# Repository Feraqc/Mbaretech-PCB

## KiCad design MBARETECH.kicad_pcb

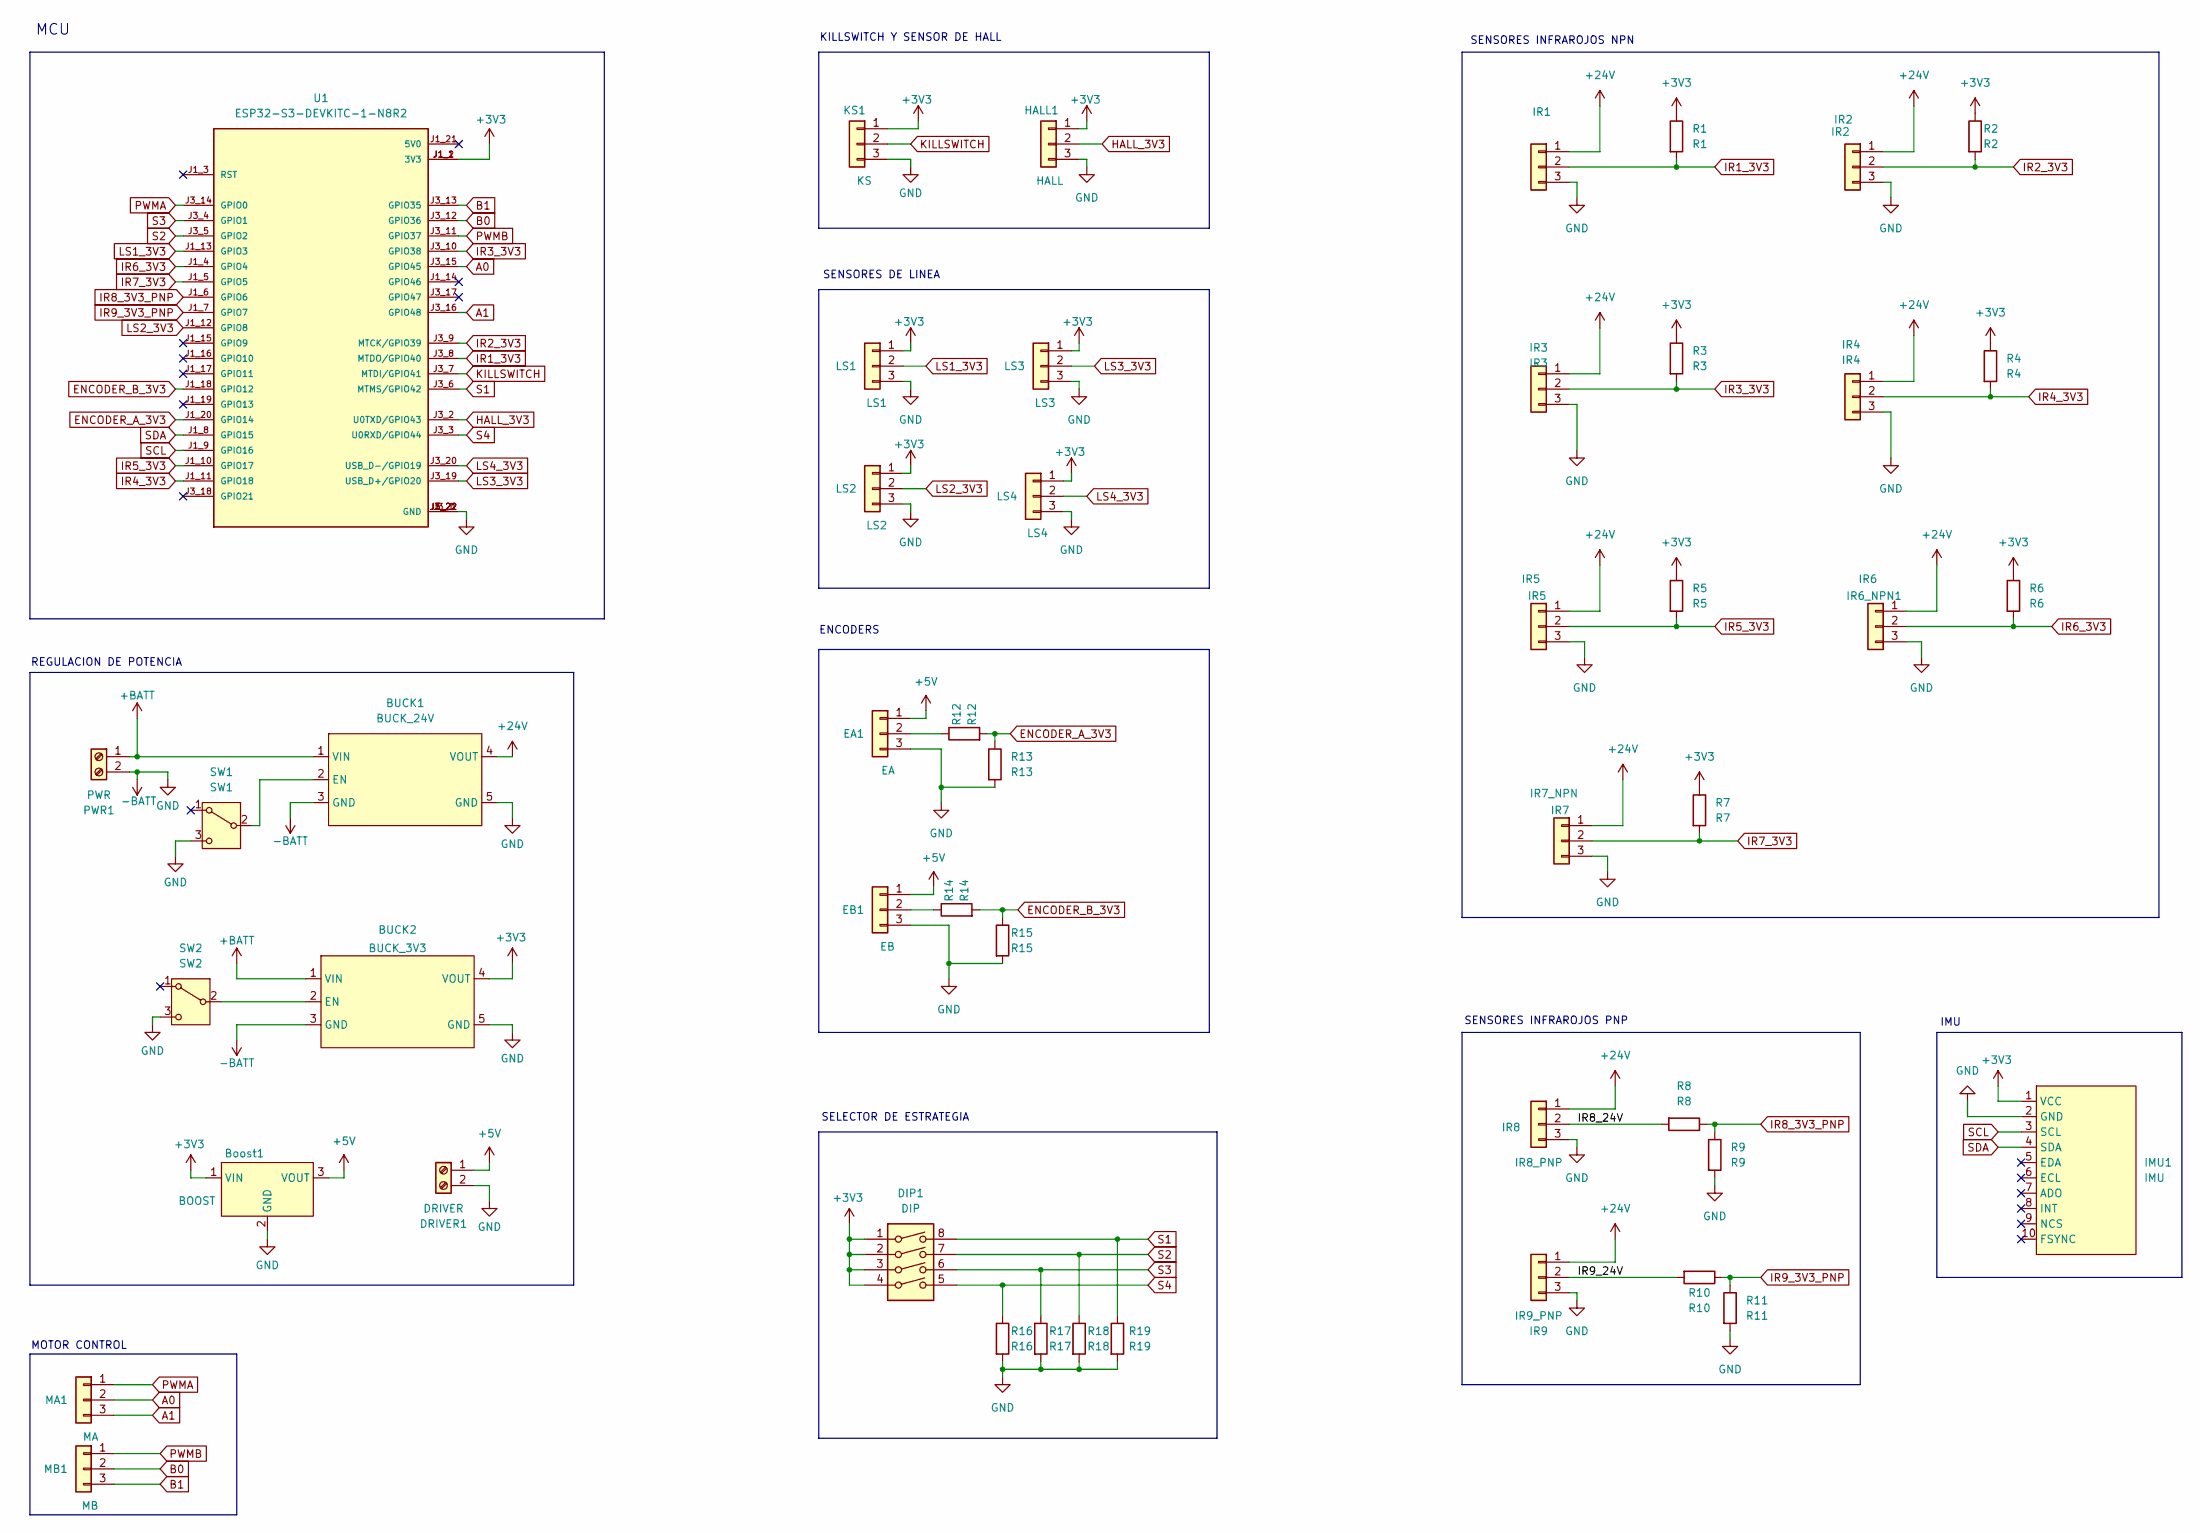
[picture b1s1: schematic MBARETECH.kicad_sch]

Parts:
BUCK1: BUCK_24V; Buck-Converter
BUCK2: BUCK_3V3; Buck-Converter
Boost1: BOOST; PinHeader_1x03_P2.54mm_Vertical
DIP1: DIP; SW_DIP_SPSTx04_Slide_9.78x12.34mm_W7.62mm_P2.54mm
DRIVER1: DRIVER; TerminalBlock_Phoenix_MKDS-1,5-2-5.08_1x02_P5.08mm_Horizont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
EA1: EA; JST_XH_B3B-XH-A_1x03_P2.50mm_Vertical
EB1: EB; JST_XH_B3B-XH-A_1x03_P2.50mm_Vertical
HALL1: HALL; JST_XH_B3B-XH-A_1x03_P2.50mm_Vertical
IMU1: IMU; PinHeader_1x10_P2.54mm_Vertical
IR1: IR1; JST_XH_B3B-XH-A_1x03_P2.50mm_Vertical
IR2: IR2; JST_XH_B3B-XH-A_1x03_P2.50mm_Vertical
IR3: IR3; JST_XH_B3B-XH-A_1x03_P2.50mm_Vertical
IR4: IR4; JST_XH_B3B-XH-A_1x03_P2.50mm_Vertical
IR5: IR5; JST_XH_B3B-XH-A_1x03_P2.50mm_Vertical
IR6_NPN1: IR6; JST_XH_B3B-XH-A_1x03_P2.50mm_Vertical
IR7: IR7_NPN; JST_XH_B3B-XH-A_1x03_P2.50mm_Vertical
IR8: IR8_PNP; JST_XH_B3B-XH-A_1x03_P2.50mm_Vertical
IR9: IR9_PNP; JST_XH_B3B-XH-A_1x03_P2.50mm_Vertical
KS1: KS; JST_XH_B3B-XH-A_1x03_P2.50mm_Vertical
LS1: LS1; JST_XH_B3B-XH-A_1x03_P2.50mm_Vertical
LS2: LS2; JST_XH_B3B-XH-A_1x03_P2.50mm_Vertical
LS3: LS3; JST_XH_B3B-XH-A_1x03_P2.50mm_Vertical
LS4: LS4; JST_XH_B3B-XH-A_1x03_P2.50mm_Vertical
MA1: MA; JST_XH_B3B-XH-A_1x03_P2.50mm_Vertical
MB1: MB; JST_XH_B3B-XH-A_1x03_P2.50mm_Vertical
PWR1: PWR; TerminalBlock_Phoenix_MKDS-1,5-2-5.08_1x02_P5.08mm_Horizont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
R1: R1; R_0603_1608Metric_Pad0.98x0.95mm_HandSolder
R2: R2; R_0603_1608Metric_Pad0.98x0.95mm_HandSolder
R3: R3; R_0603_1608Metric_Pad0.98x0.95mm_HandSolder
R4: R4; R_0603_1608Metric_Pad0.98x0.95mm_HandSolder
R5: R5; R_0603_1608Metric_Pad0.98x0.95mm_HandSolder
R6: R6; R_0603_1608Metric_Pad0.98x0.95mm_HandSolder
R7: R7; R_0603_1608Metric_Pad0.98x0.95mm_HandSolder
R8: R8; R_0603_1608Metric_Pad0.98x0.95mm_HandSolder
R9: R9; R_0603_1608Metric_Pad0.98x0.95mm_HandSolder
R10: R10; R_0603_1608Metric_Pad0.98x0.95mm_HandSolder
R11: R11; R_0603_1608Metric_Pad0.98x0.95mm_HandSolder
R12: R12; R_0603_1608Metric_Pad0.98x0.95mm_HandSolder
R13: R13; R_0603_1608Metric_Pad0.98x0.95mm_HandSolder
R14: R14; R_0603_1608Metric_Pad0.98x0.95mm_HandSolder
R15: R15; R_0603_1608Metric_Pad0.98x0.95mm_HandSolder
R16: R16; R_0603_1608Metric_Pad0.98x0.95mm_HandSolder
R17: R17; R_0603_1608Metric_Pad0.98x0.95mm_HandSolder
R18: R18; R_0603_1608Metric_Pad0.98x0.95mm_HandSolder
R19: R19; R_0603_1608Metric_Pad0.98x0.95mm_HandSolder
SW1: SW1; tht
SW2: SW2; tht
U1: ESP32-S3-DEVKITC-1-N8R2; XCVR_ESP32-S3-DEVKITC-1-N8R2; PARTREV V1

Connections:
+3V3: BUCK2.4 (VOUT), Boost1.1 (VIN), DIP1.1, DIP1.2, DIP1.3, DIP1.4, HALL1.1, IMU1.1 (VCC), KS1.1, LS1.1, LS2.1, LS3.1, LS4.1, R1.1, R2.1, R3.1, R4.1, R5.1, R6.1, R7.1, U1.J1_1 (3V3), U1.J1_2 (3V3)
+5V: Boost1.3 (VOUT), DRIVER1.1, EA1.1, EB1.1
+24V: BUCK1.4 (VOUT), IR1.1, IR2.1, IR3.1, IR4.1, IR5.1, IR6_NPN1.1, IR7.1, IR8.1, IR9.1
+BATT: BUCK1.1 (VIN), BUCK2.1 (VIN), PWR1.1
-BATT: BUCK1.3 (GND), BUCK1.5 (GND), BUCK2.3 (GND), BUCK2.5 (GND), Boost1.2 (GND), DRIVER1.2, EA1.3, EB1.3, HALL1.3, IMU1.2 (GND), IR1.3, IR2.3, IR3.3, IR4.3, IR5.3, IR6_NPN1.3, IR7.3, IR8.3, IR9.3, KS1.3, LS1.3, LS2.3, LS3.3, LS4.3, PWR1.2, R9.2, R11.2, R13.2, R15.2, R16.2, R17.2, R18.2, R19.2, SW1.3 (C), SW2.3 (C), U1.J1_22 (GND), U1.J3_1 (GND), U1.J3_21 (GND), U1.J3_22 (GND)
/IR8_24V: IR8.2, R8.2
/IR9_24V: IR9.2, R10.2
A0: MA1.2, U1.J3_15 (GPIO45)
A1: MA1.3, U1.J3_16 (GPIO48)
B0: MB1.2, U1.J3_12 (GPIO36)
B1: MB1.3, U1.J3_13 (GPIO35)
ENCODER_A_3V3: R12.2, R13.1, U1.J1_20 (GPIO14)
ENCODER_B_3V3: R14.2, R15.1, U1.J1_18 (GPIO12)
HALL_3V3: HALL1.2, U1.J3_2 (U0TXD/GPIO43)
IR1_3V3: IR1.2, R1.2, U1.J3_8 (MTDO/GPIO40)
IR2_3V3: IR2.2, R2.2, U1.J3_9 (MTCK/GPIO39)
IR3_3V3: IR3.2, R3.2, U1.J3_10 (GPIO38)
IR4_3V3: IR4.2, R4.2, U1.J1_11 (GPIO18)
IR5_3V3: IR5.2, R5.2, U1.J1_10 (GPIO17)
IR6_3V3: IR6_NPN1.2, R6.2, U1.J1_4 (GPIO4)
IR7_3V3: IR7.2, R7.2, U1.J1_5 (GPIO5)
IR8_3V3_PNP: R8.1, R9.1, U1.J1_6 (GPIO6)
IR9_3V3_PNP: R10.1, R11.1, U1.J1_7 (GPIO7)
KILLSWITCH: KS1.2, U1.J3_7 (MTDI/GPIO41)
LS1_3V3: LS1.2, U1.J1_13 (GPIO3)
LS2_3V3: LS2.2, U1.J1_12 (GPIO8)
LS3_3V3: LS3.2, U1.J3_19 (USB_D+/GPIO20)
LS4_3V3: LS4.2, U1.J3_20 (USB_D-/GPIO19)
unnamed: BUCK1.2 (EN), SW1.2 (B)
unnamed: BUCK2.2 (EN), SW2.2 (B)
unnamed: EA1.2, R12.1
unnamed: EB1.2, R14.1
PWMA: MA1.1, U1.J3_14 (GPIO0)
PWMB: MB1.1, U1.J3_11 (GPIO37)
S1: DIP1.8, R19.1, U1.J3_6 (MTMS/GPIO42)
S2: DIP1.7, R18.1, U1.J3_5 (GPIO2)
S3: DIP1.6, R17.1, U1.J3_4 (GPIO1)
S4: DIP1.5, R16.1, U1.J3_3 (U0RXD/GPIO44)
SCL: IMU1.3 (SCL), U1.J1_9 (GPIO16)
SDA: IMU1.4 (SDA), U1.J1_8 (GPIO15)

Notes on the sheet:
SENSORES DE LINEA
SELECTOR DE ESTRATEGIA
REGULACION DE POTENCIA
SENSORES INFRAROJOS NPN
IMU
KILLSWITCH Y SENSOR DE HALL
ENCODERS
SENSORES INFRAROJOS PNP
MCU
MOTOR CONTROL

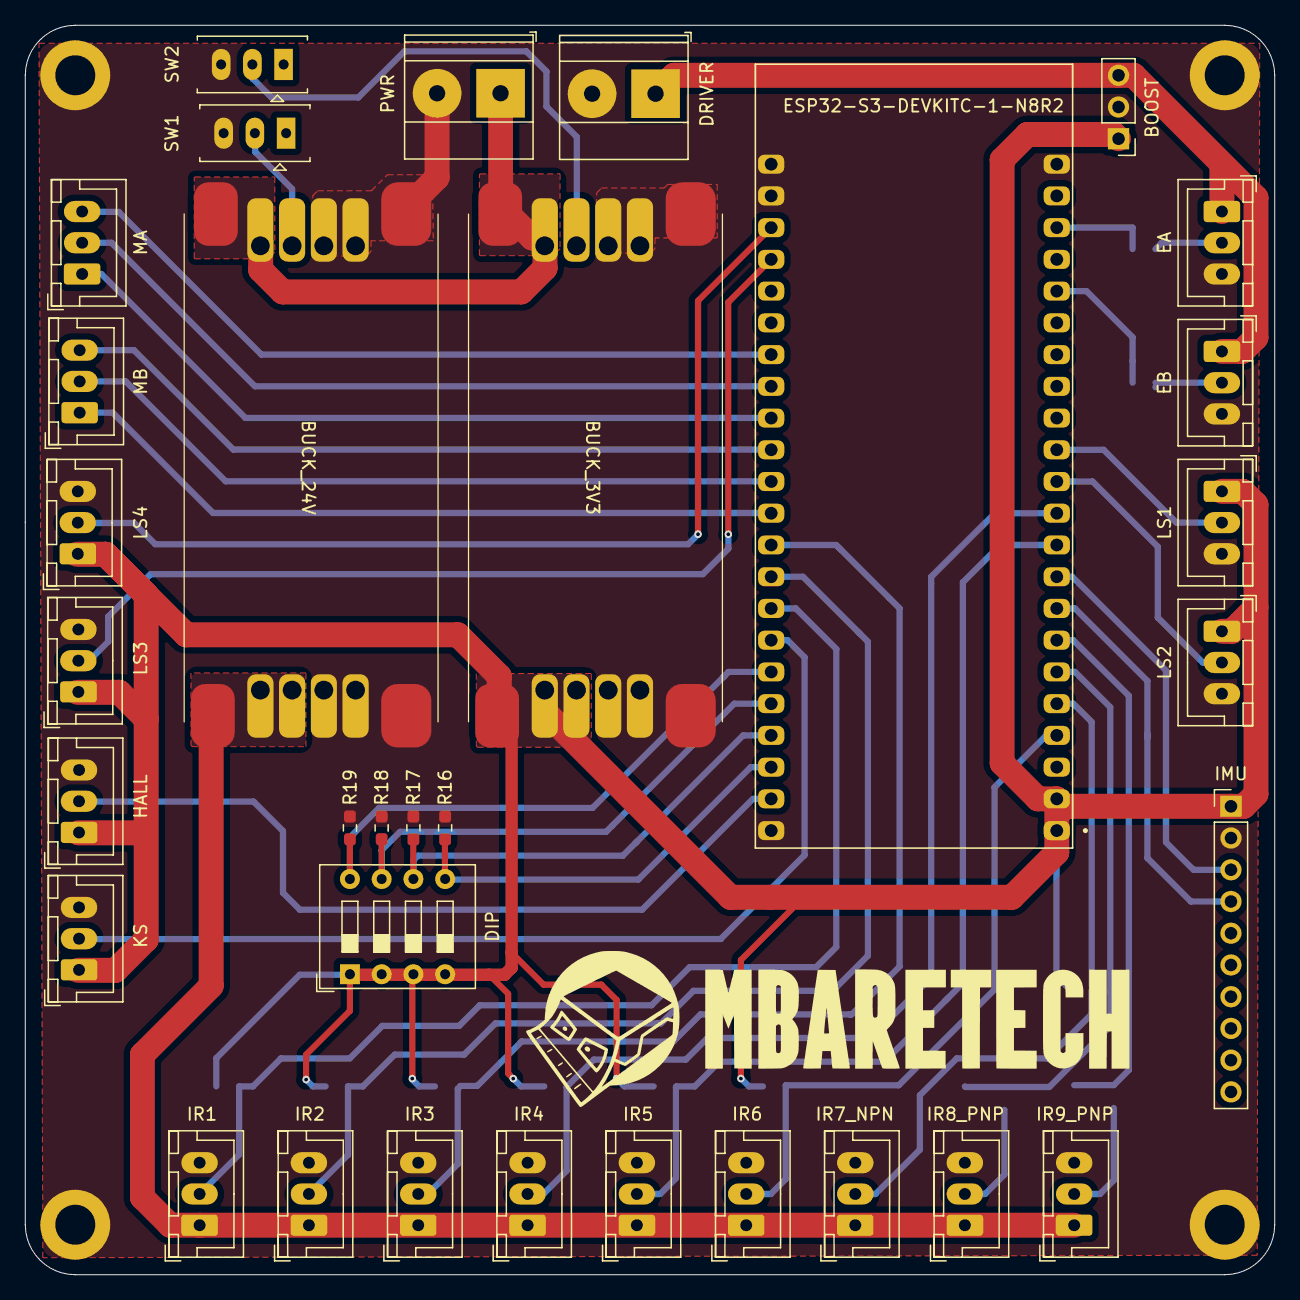
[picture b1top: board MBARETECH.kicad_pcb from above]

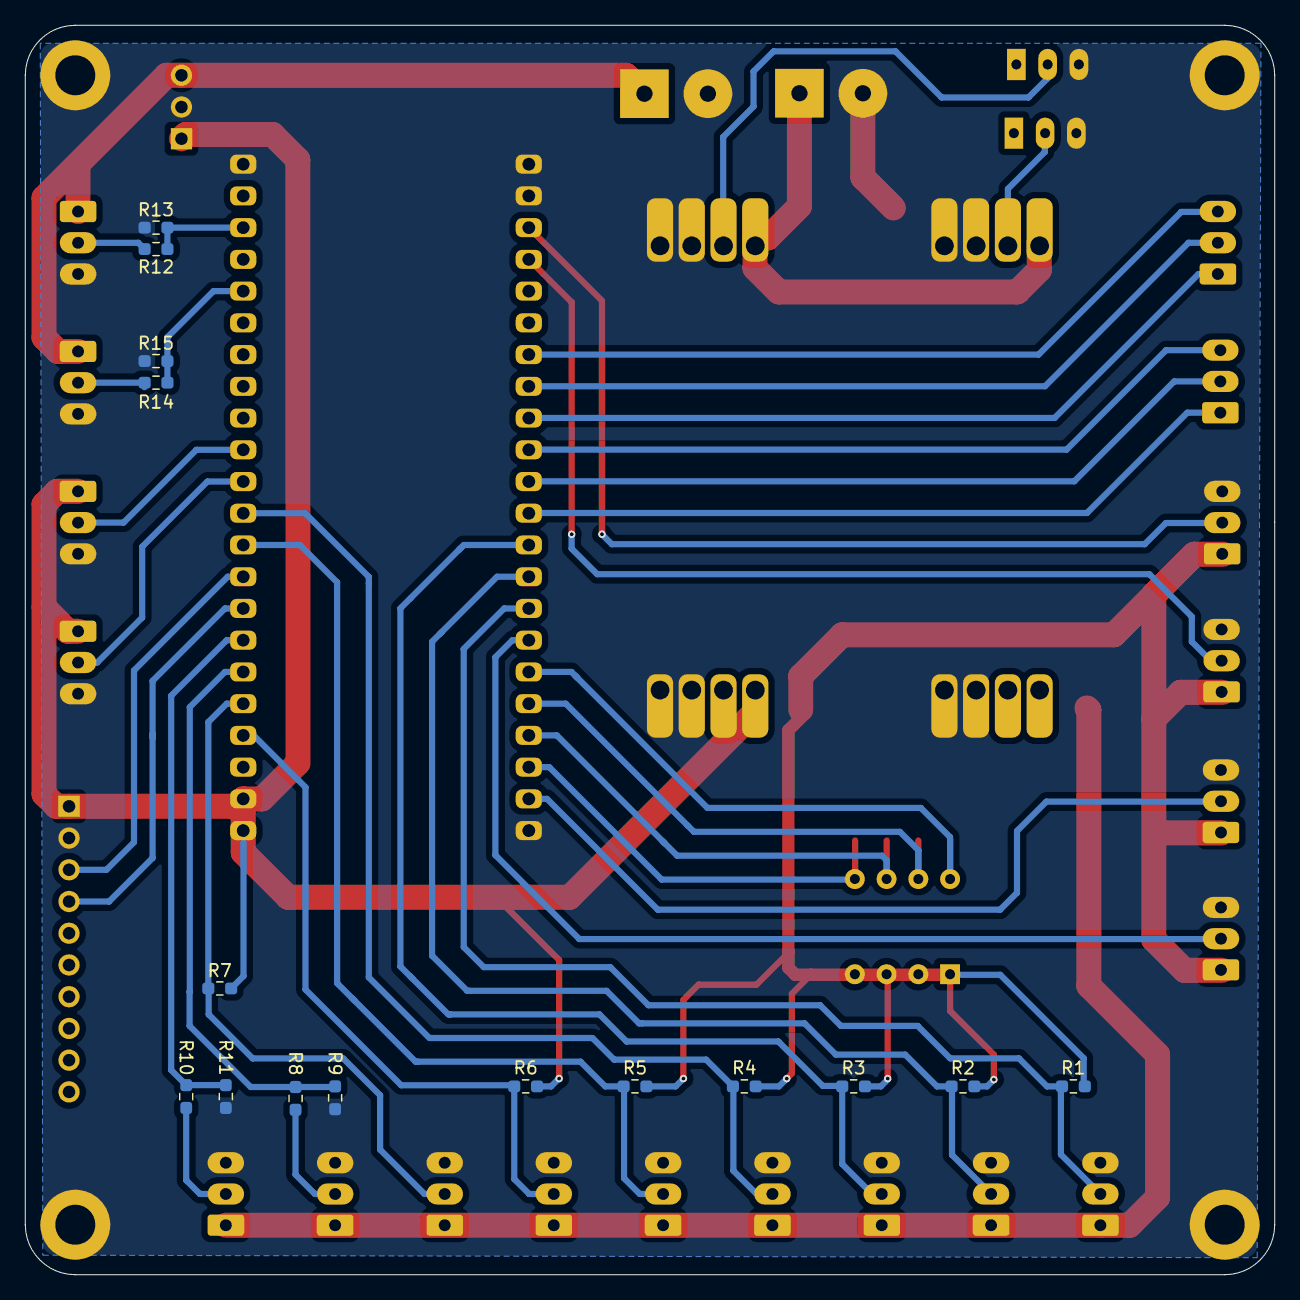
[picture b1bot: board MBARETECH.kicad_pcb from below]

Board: 2 copper layers, 100.0 x 100.0 mm, 48 parts (15 on the bottom side), 40 nets.

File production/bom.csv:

Designator,Footprint,Quantity,Value,LCSC Part #
"_4, _3, _2, ",,4,,
BUCK1,Buck-Converter,1,BUCK_24V,
BUCK2,Buck-Converter,1,BUCK_3V3,
Boost1,PinHeader_1x03_P2.54mm_Vertical,1,BOOST,
DIP1,SW_DIP_SPSTx04_Slide_9.78x12.34mm_W7.62mm_P2.54mm,1,DIP,
DRIVER1,"TerminalBlock_Phoenix_MKDS-1,5-2-5.08_1x02_P5.08mm_Horizontal",1,DRIVER,
EA1,JST_XH_B3B-XH-A_1x03_P2.50mm_Vertical,1,EA,
EB1,JST_XH_B3B-XH-A_1x03_P2.50mm_Vertical,1,EB,
HALL1,JST_XH_B3B-XH-A_1x03_P2.50mm_Vertical,1,HALL,
IMU1,PinHeader_1x10_P2.54mm_Vertical,1,IMU,
IR1,JST_XH_B3B-XH-A_1x03_P2.50mm_Vertical,1,IR1,
IR2,JST_XH_B3B-XH-A_1x03_P2.50mm_Vertical,1,IR2,
IR3,JST_XH_B3B-XH-A_1x03_P2.50mm_Vertical,1,IR3,
IR4,JST_XH_B3B-XH-A_1x03_P2.50mm_Vertical,1,IR4,
IR5,JST_XH_B3B-XH-A_1x03_P2.50mm_Vertical,1,IR5,
IR6_NPN1,JST_XH_B3B-XH-A_1x03_P2.50mm_Vertical,1,IR6,
IR7,JST_XH_B3B-XH-A_1x03_P2.50mm_Vertical,1,IR7_NPN,
IR8,JST_XH_B3B-XH-A_1x03_P2.50mm_Vertical,1,IR8_PNP,
IR9,JST_XH_B3B-XH-A_1x03_P2.50mm_Vertical,1,IR9_PNP,
KS1,JST_XH_B3B-XH-A_1x03_P2.50mm_Vertical,1,KS,
LS1,JST_XH_B3B-XH-A_1x03_P2.50mm_Vertical,1,LS1,
LS2,JST_XH_B3B-XH-A_1x03_P2.50mm_Vertical,1,LS2,
LS3,JST_XH_B3B-XH-A_1x03_P2.50mm_Vertical,1,LS3,
LS4,JST_XH_B3B-XH-A_1x03_P2.50mm_Vertical,1,LS4,
MA1,JST_XH_B3B-XH-A_1x03_P2.50mm_Vertical,1,MA,
MB1,JST_XH_B3B-XH-A_1x03_P2.50mm_Vertical,1,MB,
PWR1,"TerminalBlock_Phoenix_MKDS-1,5-2-5.08_1x02_P5.08mm_Horizontal",1,PWR,
R1,0603,1,R1,
R10,0603,1,R10,
R11,0603,1,R11,
R12,0603,1,R12,
R13,0603,1,R13,
R14,0603,1,R14,
R15,0603,1,R15,
R16,0603,1,R16,
R17,0603,1,R17,
R18,0603,1,R18,
R19,0603,1,R19,
R2,0603,1,R2,
R3,0603,1,R3,
R4,0603,1,R4,
R5,0603,1,R5,
R6,0603,1,R6,
R7,0603,1,R7,
R8,0603,1,R8,
R9,0603,1,R9,
SW1,tht,1,SW1,
SW2,tht,1,SW2,
U1,XCVR_ESP32-S3-DEVKITC-1-N8R2,1,ESP32-S3-DEVKITC-1-N8R2,

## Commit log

2024-03-21 added files
2024-03-21 test branch
2024-03-21 Primera iteracion
2024-05-02 Version final
2024-05-02 Connect -BATT2GND
2024-05-02 Version final revision
2024-05-02 logo fix
2024-05-02 production files added
2024-05-02 final
2024-06-29 mini PCB added
2024-06-29 Schematic pdf added
2024-07-01 step file added
